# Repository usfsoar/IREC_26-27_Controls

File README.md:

# University of South Florida (USF)
# Society of Aeronautics and Rocketry (SOAR)
## International Rocket Engineering Competition (IREC) Team
## Controls Subsystem Repository

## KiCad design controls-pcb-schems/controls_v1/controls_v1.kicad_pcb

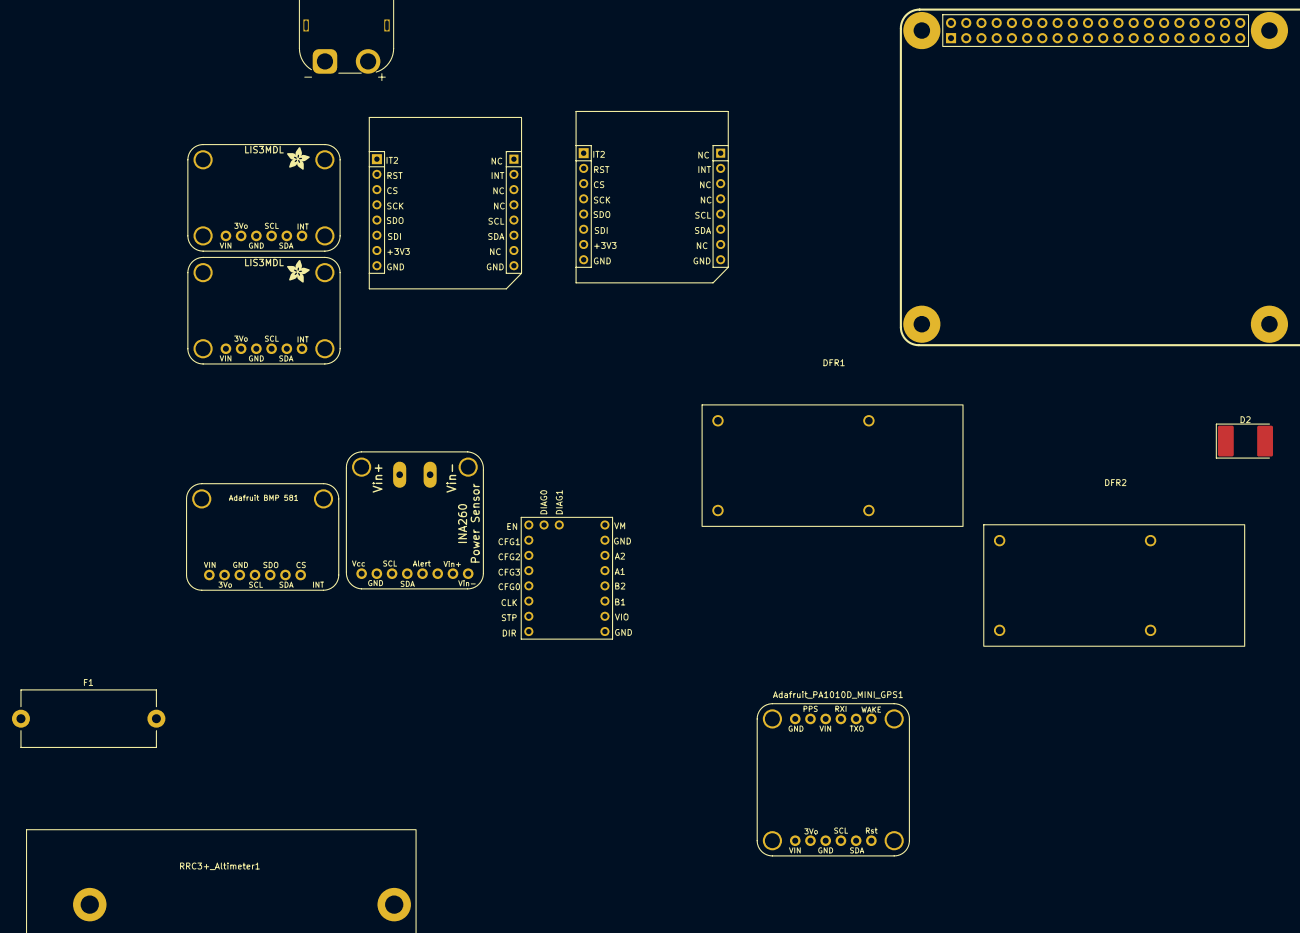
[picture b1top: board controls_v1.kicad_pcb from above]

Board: 2 copper layers, 15 parts (0 on the bottom side), 16 nets, no tracks yet.

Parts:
Adafruit_PA1010D_MINI_GPS1: Adafruit_PA1010D_Mini_GPS
BIGTREEETECH_TMC5160T1: BIGTREETECH TMC5160T
D2: D_Schottky; D_3220_8050Metric_Pad2.65x5.15mm_HandSolder
DFR1, DFR2: DFR0831 DC-DC
F1: Fuse; Fuseholder_Cylinder-5x20mm_Stelvio-Kontek_PTF78_Horizontal_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
IC1: Adafruit INA260
IC2, IC3: Adafruit LIS3MDL
J1: XT60PW-F; AMASS_XT60PW-M_1x02_P7.20mm_Horizontal
MIKROE-1, MIKROE-2: MIKROBUS_MODULE_CONN
RRC3+_Altimeter1: RRC3+ Altimeter
U1: Adafruit BMP581
U6: Raspberry Pi 4 Pins

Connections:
+3.3V: MIKROE-1.7 (3V3_P7), MIKROE-2.7 (3V3_P7), U6.1 (3V3), U6.17 (3V3)
+3V3: IC2.1 (Vin), IC3.1 (Vin)
+BatteryV: D2.1 (K), J1.1
+MotorV: IC1.1 (IN+), IC1.2 (IN+), IC1.3 (IN+)
GND: D2.2 (A), F1.2, IC1.6 (GND), IC2.3 (GND), IC3.3 (GND), MIKROE-1.8 (GND1_P8), MIKROE-2.8 (GND1_P8), U6.6 (GND), U6.9 (GND), U6.14 (GND), U6.20 (GND), U6.25 (GND), U6.30 (GND), U6.34 (GND), U6.39 (GND)
unnamed: Adafruit_PA1010D_MINI_GPS1.2 (SCL), U6.28 (ID_SC_I2C0/GPIO01)
unnamed: Adafruit_PA1010D_MINI_GPS1.1 (SDA), IC1.8 (SDA), U6.27 (ID_SD_I2C0/GPIO00)
unnamed: MIKROE-1.4 (SCK_P4), MIKROE-2.4 (SCK_P4), U6.40 (GPIO21/SPI1_SCLK/PCM_DOUT)
unnamed: MIKROE-1.6 (MOSI_P6), MIKROE-2.6 (MOSI_P6), U6.38 (GPIO20/SPI1_MOSI/PCM_DIN/PWM1)
unnamed: MIKROE-1.5 (MISO_P5), MIKROE-2.5 (MISO_P5), U6.35 (GPIO19/SPI1_MISO/PCM_FS)
unnamed: IC2.4 (SCL/SCK), IC3.4 (SCL/SCK), U6.5 (SCL_I2C1/GPIO03)
unnamed: IC2.5 (SDA/MOSI), IC3.5 (SDA/MOSI), U6.3 (SDA_I2C1/GPIO02)
unnamed: F1.1, J1.2 (N)
unnamed: MIKROE-1.3 (CS_P3), U6.36 (GPIO16/SPI1_~CE2)
unnamed: MIKROE-2.3 (CS_P3), U6.11 (GPIO17/SPI1_~CE1)
unnamed: U6.2 (5V), U6.4 (5V)
